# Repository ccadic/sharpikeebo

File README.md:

**SHARPIKEEBO – Version 2025 (Public Release)
**

**sharpikeebo – V2025
Miniature Raspberry Pi Zero 2W shield with Sharp Memory Display and USB Keyboard
**
This repository now documents the public 2025 version of the SHARPIKEEBO, distributed after the successful crowdfunding campaign on
Crowd Supply: https://www.crowdsupply.com/morpheans/sharpikeebo

All hardware described here corresponds to the final production version delivered to backers and the public.

Overview

Hello all,

This is the SHARPIKEEBO Nano Computer Shield, built around the famous Raspberry Pi Zero 2W, featuring:

- A high-quality Sharp Memory Display (400 × 240 pixels)
- A true USB keyboard, powered by QMK firmware
(https://docs.qmk.fm/#/)
- An ATmega32U4 microcontroller
- A compact form factor designed as a real miniature Linux terminal

The SHARPIKEEBO was initially designed as a portable SSH and system administration tool, allowing administrators to quickly connect to servers and perform maintenance operations.
During development, many users also pointed out its potential as a retro or lightweight gaming platform.

**Hardware Description
**

The SHARPIKEEBO carrier board is designed to host:

- A Raspberry Pi Zero 2W or Zero W
- A 2.7" Sharp Memory Display (400 × 240) capable of fast refresh rates, suitable for:
  Linux shells
  Text-based interfaces
  Simple graphical games
  Additional features include:

- Controllable LEDs (GPIO, usable from C++ or Python)
- Easily accessible UART and I²C GPIOs for external modules:
  GPS
  4G / 5G modem
  Other 3.3 V or 5 V peripherals

Power is supplied via USB-C, and the board can also behave as a USB keyboard device when plugged into a desktop, laptop, or rack server.

**IMPORTANT CHANGES & CLARIFICATION (READ CAREFULLY)
**
This section is critical for proper operation of the 2025 public hardware.

**Raspberry Pi Zero mounting orientation (VERY IMPORTANT)
**

The Raspberry Pi Zero must be mounted with its connector facing DOWN

This means the components of the Raspberry Pi remain visible

DO NOT use a 20×2 pin header mounted on the TOP side

If the Raspberry Pi is connected using a top-mounted 20×2 pin header, the board will NOT work

 This is not optional and is required by the electrical design of the SHARPIKEEBO.

 Battery polarity warning
**** 

Some batteries on the market do NOT follow standard polarity orientation

Incorrect polarity can permanently damage the board

 Always verify battery polarity against the schematics before connecting
 Never assume wire colors are correct

**RAK Wireless module interface
**
The RAK Wireless module is connected in UART mode

It is NOT wired in SPI mode

 Any software configuration must therefore use UART, not SPI.
Factory testing guarantee

Every single SHARPIKEEBO unit shipped has been individually tested

All boards were:
- Powered
- Verified
- Confirmed fully functional before shipping

If you encounter an issue, it is almost always related to:
- Incorrect Raspberry Pi mounting
- Battery polarity inversion
- Incorrect peripheral wiring or configuration
- Status

This repository now reflects the final, stable, production hardware shipped after the Crowd Supply campaign.
Future updates will focus on software examples, configurations, and community contributions, not hardware changes.

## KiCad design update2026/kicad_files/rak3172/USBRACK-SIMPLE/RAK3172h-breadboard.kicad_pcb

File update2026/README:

Here is the update of 2026 files

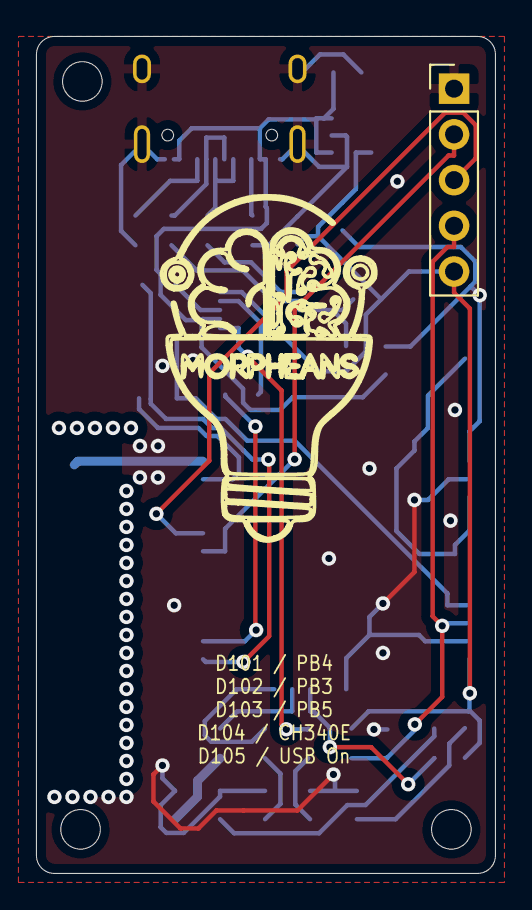
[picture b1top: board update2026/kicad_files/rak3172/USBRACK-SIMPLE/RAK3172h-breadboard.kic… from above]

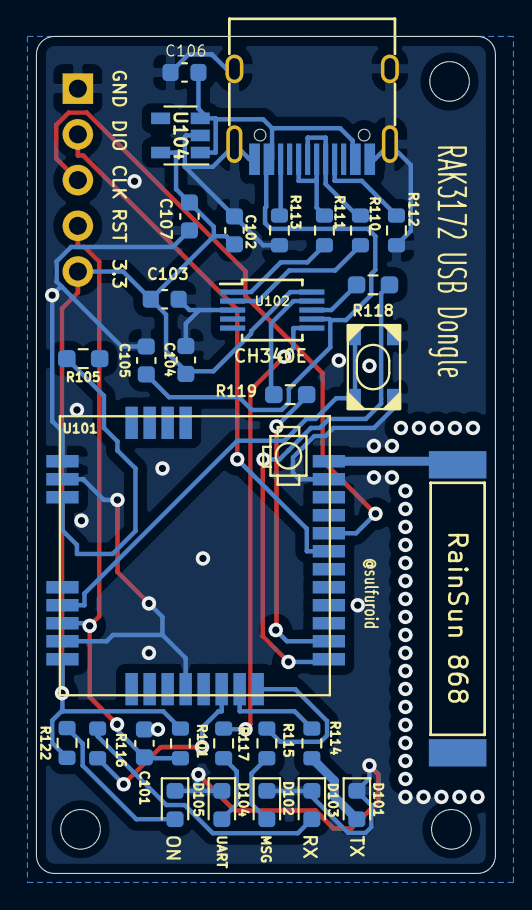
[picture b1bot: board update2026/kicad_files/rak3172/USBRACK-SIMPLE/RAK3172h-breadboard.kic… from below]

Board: 2 copper layers, 25.5 x 46.5 mm, 35 parts (31 on the bottom side), 28 nets.

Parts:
C101, C102, C104, C105: 100nF; C_0603_1608Metric
C103: 10uF; C_0603_1608Metric
C106, C107: 1uF; C_0603_1608Metric
D101: TX-YEL; LED_0603_1608Metric
D102: GreenL; LED_0603_1608Metric
D103: RX-RED; LED_0603_1608Metric
D104: Violet; LED_0603_1608Metric
D105: ON-LED; LED_0603_1608Metric
H101, H102, H103: MountingHole; MountingHole_2.2mm_M2
J101: Prog_cnx; PinHeader_1x05_P2.54mm_Vertical
J104: USB_C_Receptacle; GT-USB-7010
R101: 10k; R_0603_1608Metric
R105: 1k; R_0603_1608Metric_Pad0.98x0.95mm_HandSolder
R110, R111: 22R; R_0603_1608Metric
R112, R113: 5.1K; R_0603_1608Metric
R114, R115, R116, R122: 330R; R_0603_1608Metric
R117: 1.2k; R_0603_1608Metric
R118, R119: 0R; R_0603_1608Metric_Pad0.98x0.95mm_HandSolder
SW105: BOOT; SKRPABE010
U101: RAK3172
U102: CH340E; MSOP-10_3x3mm_P0.5mm
U103: RainSun_Antenna
U104: ME6211C33M5G-N; SOT-23-5

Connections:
+3V3: C102.2, C103.2, C104.2, C107.2, J101.5, R101.1, R122.1, U101.24, U102.10, U104.5
/BUT2: R105.1, U101.19
/RESET: C101.2, J101.4, R101.2, U101.22
/SWCLK: J101.3, U101.8
/SWDIO: J101.2, U101.7
/UART2RX: R118.1, U101.1
/UART2TX: R119.1, U101.2
/USB+: R111.2, U102.1
/USB-: R110.2, U102.2
/VUSB: C105.2, C106.2, J104.A4, J104.A9, J104.B4, J104.B9, U102.7, U104.1, U104.3
GND: C101.1, C102.1, C103.1, C104.1, C105.1, C106.1, C107.1, D101.1, D102.1, D103.1, D104.1, D105.1, J101.1, J104.A1, J104.A12, J104.B1, J104.B12, J104.S1, R112.2, R113.2, SW105.2, U101.11, U101.17, U101.18, U101.23, U101.28, U102.3, U104.2
unnamed: D101.2, R114.2
unnamed: D102.2, R115.2
unnamed: D103.2, R116.2
unnamed: D104.2, R117.2
unnamed: D105.2, R122.2
unnamed: J104.A5, R112.1
unnamed: J104.A6, J104.B6, R111.1
unnamed: J104.A7, J104.B7, R110.1
unnamed: J104.B5, R113.1
unnamed: R114.1, U101.31
unnamed: R115.1, U101.32
unnamed: R116.1, U101.30
unnamed: R117.1, U102.6
unnamed: R118.2, U102.8
unnamed: R119.2, U102.9
unnamed: SW105.1, U101.21
unnamed: U101.12, U103.1

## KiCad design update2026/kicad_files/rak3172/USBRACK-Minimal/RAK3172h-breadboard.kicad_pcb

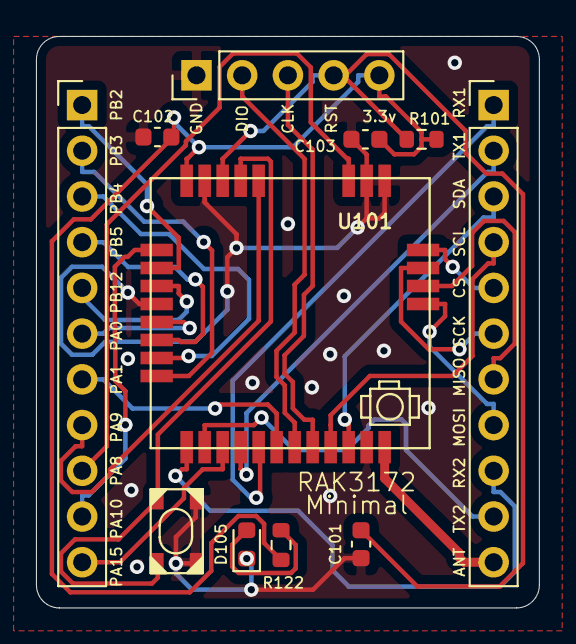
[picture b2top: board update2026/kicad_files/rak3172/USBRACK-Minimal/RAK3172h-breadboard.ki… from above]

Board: 2 copper layers, 27.9 x 31.8 mm, 11 parts (0 on the bottom side), 29 nets.

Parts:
C101, C102: 100nF; C_0603_1608Metric
C103: 10uF; C_0603_1608Metric
D105: ON-LED; LED_0603_1608Metric
J101: Prog_cnx; PinHeader_1x05_P2.54mm_Vertical
J102: GPIOA; PinHeader_1x11_P2.54mm_Vertical
J103: GPIOB; PinHeader_1x11_P2.54mm_Vertical
R101: 10k; R_0603_1608Metric
R122: 330R; R_0603_1608Metric
SW105: BOOT; SKRPABE010
U101: RAK3172

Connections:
+3V3: C102.2, C103.2, J101.5, R101.1, R122.1, U101.24
/ANT: J103.11, U101.12
/CS: J103.5, U101.16
/MISO: J103.7, U101.14
/MOSI: J103.8, U101.13
/PA0: J102.6, U101.29
/PA1: J102.7, U101.6
/PA8: J102.9, U101.19
/PA9: J102.8, U101.20
/PA10: J102.10, U101.25
/PA15: J102.11, U101.3
/PB2: J102.1, U101.26
/PB3: J102.2, U101.32
/PB4: J102.3, U101.31
/PB5: J102.4, U101.30
/PB12: J102.5, U101.27
/RESET: C101.2, J101.4, R101.2, U101.22
/RX1: J103.1, U101.5
/SCK: J103.6, U101.15
/SCL: J103.4, U101.9
/SDA: J103.3, U101.10
/SWCLK: J101.3, U101.8
/SWDIO: J101.2, U101.7
/TX1: J103.2, U101.4
/UART2RX: J103.9, U101.1
/UART2TX: J103.10, U101.2
GND: C101.1, C102.1, C103.1, D105.1, J101.1, SW105.2, U101.11, U101.17, U101.18, U101.23, U101.28
unnamed: D105.2, R122.2
unnamed: SW105.1, U101.21

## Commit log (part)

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2022-03-16 Change ATmega32U4 from MU to AU
    the ATmega32U4-MU (QFN-44_7x7x05P) is too small for the sharpikeebo
2022-03-16 Update BOM_MemoryBrakout
2026-01-12 Create DisplaySETUP
